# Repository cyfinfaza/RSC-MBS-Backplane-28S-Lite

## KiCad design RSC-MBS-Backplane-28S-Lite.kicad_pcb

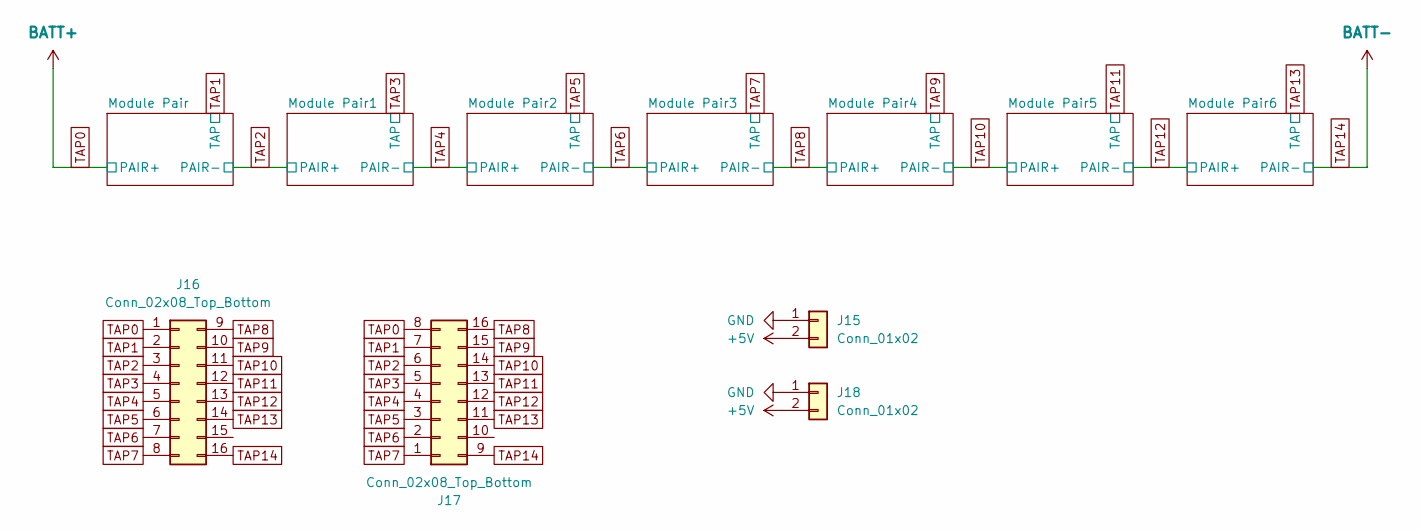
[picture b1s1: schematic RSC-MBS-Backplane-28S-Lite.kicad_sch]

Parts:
J15, J18: Conn_01x02; Molex_Micro-Fit_3.0_43650-0200_1x02_P3.00mm_Horizontal
J16, J17: Conn_02x08_Top_Bottom; Molex_Micro-Fit_3.0_43045-1600_2x08_P3.00mm_Horizontal

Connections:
+5V: J15.2, J18.2; also elsewhere on the board
GND: J15.1, J18.1; also elsewhere on the board
TAP0: J16.1, J17.8; also elsewhere on the board
TAP1: J16.2, J17.7; also elsewhere on the board
TAP2: J16.3, J17.6; also elsewhere on the board
TAP3: J16.4, J17.5; also elsewhere on the board
TAP4: J16.5, J17.4; also elsewhere on the board
TAP5: J16.6, J17.3; also elsewhere on the board
TAP6: J16.7, J17.2; also elsewhere on the board
TAP7: J16.8, J17.1; also elsewhere on the board
TAP8: J16.9, J17.16; also elsewhere on the board
TAP9: J16.10, J17.15; also elsewhere on the board
TAP10: J16.11, J17.14; also elsewhere on the board
TAP11: J16.12, J17.13; also elsewhere on the board
TAP12: J16.13, J17.12; also elsewhere on the board
TAP13: J16.14, J17.11; also elsewhere on the board
TAP14: J16.16, J17.9; also elsewhere on the board

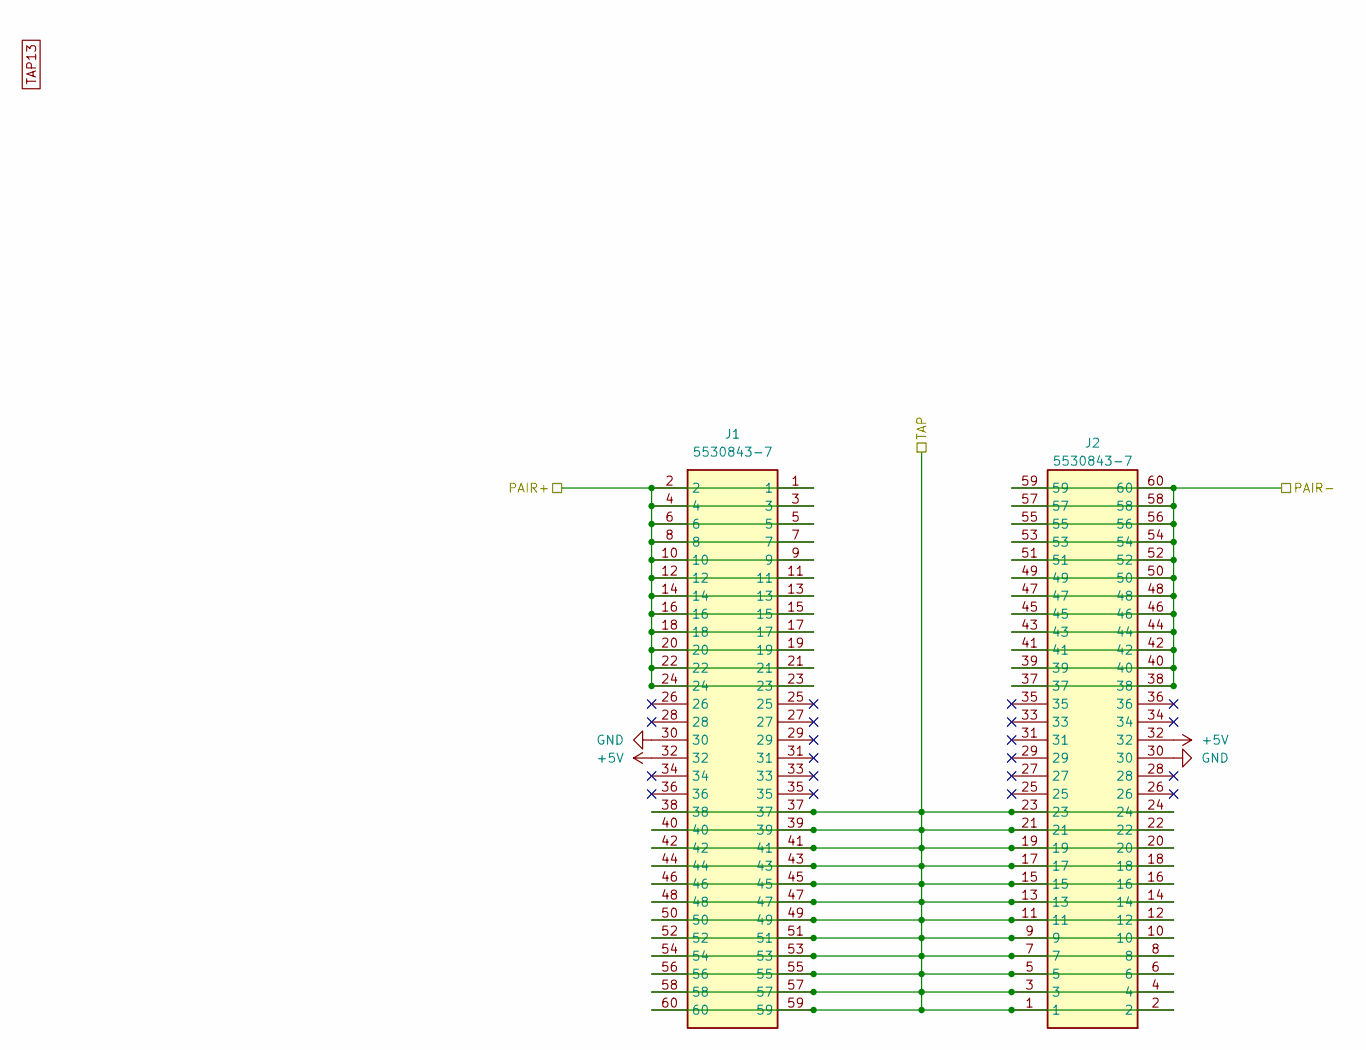
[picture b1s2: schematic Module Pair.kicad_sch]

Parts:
J1, J2: 5530843-7; 55308437; Mouser Part Number 571-5530843-7

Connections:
+5V: J1.32, J2.32; also elsewhere on the board
GND: J1.30, J2.30; also elsewhere on the board
TAP0: J1.1, J1.2, J1.3, J1.4, J1.5, J1.6, J1.7, J1.8, J1.9, J1.10, J1.11, J1.12, J1.13, J1.14, J1.15, J1.16, J1.17, J1.18, J1.19, J1.20, J1.21, J1.22, J1.23, J1.24; also elsewhere on the board
TAP1: J1.37, J1.38, J1.39, J1.40, J1.41, J1.42, J1.43, J1.44, J1.45, J1.46, J1.47, J1.48, J1.49, J1.50, J1.51, J1.52, J1.53, J1.54, J1.55, J1.56, J1.57, J1.58, J1.59, J1.60, J2.1, J2.2, J2.3, J2.4, J2.5, J2.6, J2.7, J2.8, J2.9, J2.10, J2.11, J2.12, J2.13, J2.14, J2.15, J2.16, J2.17, J2.18, J2.19, J2.20, J2.21, J2.22, J2.23, J2.24; also elsewhere on the board
TAP2: J2.37, J2.38, J2.39, J2.40, J2.41, J2.42, J2.43, J2.44, J2.45, J2.46, J2.47, J2.48, J2.49, J2.50, J2.51, J2.52, J2.53, J2.54, J2.55, J2.56, J2.57, J2.58, J2.59, J2.60; also elsewhere on the board

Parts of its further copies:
J3, J4, J5, J6, J7, J8, J9, J10, J11, J12, J13, J14: 5530843-7; 55308437; Mouser Part Number 571-5530843-7

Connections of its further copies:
+5V: J3.32, J4.32, J5.32, J6.32, J7.32, J8.32, J9.32, J10.32, J11.32, J12.32, J13.32, J14.32; also elsewhere on the board
GND: J3.30, J4.30, J5.30, J6.30, J7.30, J8.30, J9.30, J10.30, J11.30, J12.30, J13.30, J14.30; also elsewhere on the board
TAP2: J3.1, J3.2, J3.3, J3.4, J3.5, J3.6, J3.7, J3.8, J3.9, J3.10, J3.11, J3.12, J3.13, J3.14, J3.15, J3.16, J3.17, J3.18, J3.19, J3.20, J3.21, J3.22, J3.23, J3.24; also elsewhere on the board
TAP3: J3.37, J3.38, J3.39, J3.40, J3.41, J3.42, J3.43, J3.44, J3.45, J3.46, J3.47, J3.48, J3.49, J3.50, J3.51, J3.52, J3.53, J3.54, J3.55, J3.56, J3.57, J3.58, J3.59, J3.60, J4.1, J4.2, J4.3, J4.4, J4.5, J4.6, J4.7, J4.8, J4.9, J4.10, J4.11, J4.12, J4.13, J4.14, J4.15, J4.16, J4.17, J4.18, J4.19, J4.20, J4.21, J4.22, J4.23, J4.24; also elsewhere on the board
TAP4: J4.37, J4.38, J4.39, J4.40, J4.41, J4.42, J4.43, J4.44, J4.45, J4.46, J4.47, J4.48, J4.49, J4.50, J4.51, J4.52, J4.53, J4.54, J4.55, J4.56, J4.57, J4.58, J4.59, J4.60, J5.1, J5.2, J5.3, J5.4, J5.5, J5.6, J5.7, J5.8, J5.9, J5.10, J5.11, J5.12, J5.13, J5.14, J5.15, J5.16, J5.17, J5.18, J5.19, J5.20, J5.21, J5.22, J5.23, J5.24; also elsewhere on the board
TAP5: J5.37, J5.38, J5.39, J5.40, J5.41, J5.42, J5.43, J5.44, J5.45, J5.46, J5.47, J5.48, J5.49, J5.50, J5.51, J5.52, J5.53, J5.54, J5.55, J5.56, J5.57, J5.58, J5.59, J5.60, J6.1, J6.2, J6.3, J6.4, J6.5, J6.6, J6.7, J6.8, J6.9, J6.10, J6.11, J6.12, J6.13, J6.14, J6.15, J6.16, J6.17, J6.18, J6.19, J6.20, J6.21, J6.22, J6.23, J6.24; also elsewhere on the board
TAP6: J6.37, J6.38, J6.39, J6.40, J6.41, J6.42, J6.43, J6.44, J6.45, J6.46, J6.47, J6.48, J6.49, J6.50, J6.51, J6.52, J6.53, J6.54, J6.55, J6.56, J6.57, J6.58, J6.59, J6.60, J7.1, J7.2, J7.3, J7.4, J7.5, J7.6, J7.7, J7.8, J7.9, J7.10, J7.11, J7.12, J7.13, J7.14, J7.15, J7.16, J7.17, J7.18, J7.19, J7.20, J7.21, J7.22, J7.23, J7.24; also elsewhere on the board
TAP7: J7.37, J7.38, J7.39, J7.40, J7.41, J7.42, J7.43, J7.44, J7.45, J7.46, J7.47, J7.48, J7.49, J7.50, J7.51, J7.52, J7.53, J7.54, J7.55, J7.56, J7.57, J7.58, J7.59, J7.60, J8.1, J8.2, J8.3, J8.4, J8.5, J8.6, J8.7, J8.8, J8.9, J8.10, J8.11, J8.12, J8.13, J8.14, J8.15, J8.16, J8.17, J8.18, J8.19, J8.20, J8.21, J8.22, J8.23, J8.24; also elsewhere on the board
TAP8: J8.37, J8.38, J8.39, J8.40, J8.41, J8.42, J8.43, J8.44, J8.45, J8.46, J8.47, J8.48, J8.49, J8.50, J8.51, J8.52, J8.53, J8.54, J8.55, J8.56, J8.57, J8.58, J8.59, J8.60, J9.1, J9.2, J9.3, J9.4, J9.5, J9.6, J9.7, J9.8, J9.9, J9.10, J9.11, J9.12, J9.13, J9.14, J9.15, J9.16, J9.17, J9.18, J9.19, J9.20, J9.21, J9.22, J9.23, J9.24; also elsewhere on the board
TAP9: J9.37, J9.38, J9.39, J9.40, J9.41, J9.42, J9.43, J9.44, J9.45, J9.46, J9.47, J9.48, J9.49, J9.50, J9.51, J9.52, J9.53, J9.54, J9.55, J9.56, J9.57, J9.58, J9.59, J9.60, J10.1, J10.2, J10.3, J10.4, J10.5, J10.6, J10.7, J10.8, J10.9, J10.10, J10.11, J10.12, J10.13, J10.14, J10.15, J10.16, J10.17, J10.18, J10.19, J10.20, J10.21, J10.22, J10.23, J10.24; also elsewhere on the board
TAP10: J10.37, J10.38, J10.39, J10.40, J10.41, J10.42, J10.43, J10.44, J10.45, J10.46, J10.47, J10.48, J10.49, J10.50, J10.51, J10.52, J10.53, J10.54, J10.55, J10.56, J10.57, J10.58, J10.59, J10.60, J11.1, J11.2, J11.3, J11.4, J11.5, J11.6, J11.7, J11.8, J11.9, J11.10, J11.11, J11.12, J11.13, J11.14, J11.15, J11.16, J11.17, J11.18, J11.19, J11.20, J11.21, J11.22, J11.23, J11.24; also elsewhere on the board
TAP11: J11.37, J11.38, J11.39, J11.40, J11.41, J11.42, J11.43, J11.44, J11.45, J11.46, J11.47, J11.48, J11.49, J11.50, J11.51, J11.52, J11.53, J11.54, J11.55, J11.56, J11.57, J11.58, J11.59, J11.60, J12.1, J12.2, J12.3, J12.4, J12.5, J12.6, J12.7, J12.8, J12.9, J12.10, J12.11, J12.12, J12.13, J12.14, J12.15, J12.16, J12.17, J12.18, J12.19, J12.20, J12.21, J12.22, J12.23, J12.24; also elsewhere on the board
TAP12: J12.37, J12.38, J12.39, J12.40, J12.41, J12.42, J12.43, J12.44, J12.45, J12.46, J12.47, J12.48, J12.49, J12.50, J12.51, J12.52, J12.53, J12.54, J12.55, J12.56, J12.57, J12.58, J12.59, J12.60, J13.1, J13.2, J13.3, J13.4, J13.5, J13.6, J13.7, J13.8, J13.9, J13.10, J13.11, J13.12, J13.13, J13.14, J13.15, J13.16, J13.17, J13.18, J13.19, J13.20, J13.21, J13.22, J13.23, J13.24; also elsewhere on the board
TAP13: J13.37, J13.38, J13.39, J13.40, J13.41, J13.42, J13.43, J13.44, J13.45, J13.46, J13.47, J13.48, J13.49, J13.50, J13.51, J13.52, J13.53, J13.54, J13.55, J13.56, J13.57, J13.58, J13.59, J13.60, J14.1, J14.2, J14.3, J14.4, J14.5, J14.6, J14.7, J14.8, J14.9, J14.10, J14.11, J14.12, J14.13, J14.14, J14.15, J14.16, J14.17, J14.18, J14.19, J14.20, J14.21, J14.22, J14.23, J14.24; also elsewhere on the board
TAP14: J14.37, J14.38, J14.39, J14.40, J14.41, J14.42, J14.43, J14.44, J14.45, J14.46, J14.47, J14.48, J14.49, J14.50, J14.51, J14.52, J14.53, J14.54, J14.55, J14.56, J14.57, J14.58, J14.59, J14.60; also elsewhere on the board

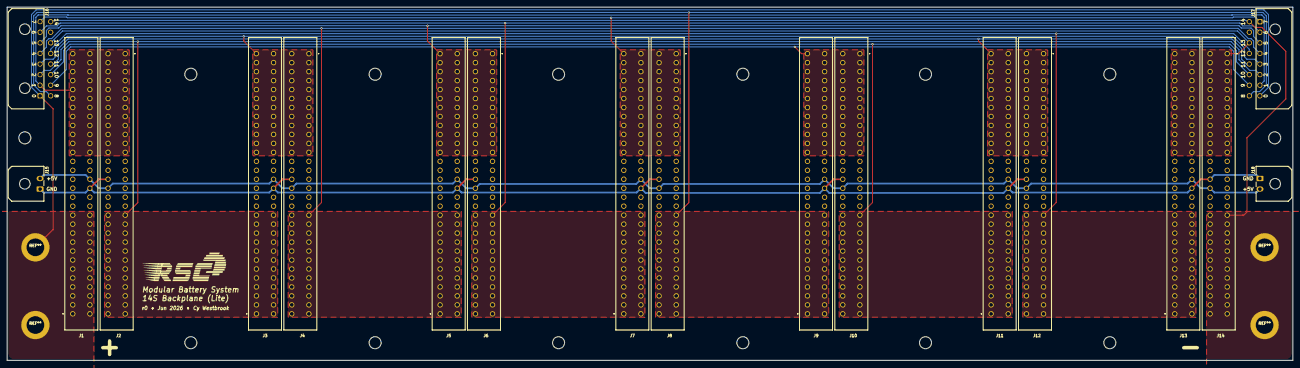
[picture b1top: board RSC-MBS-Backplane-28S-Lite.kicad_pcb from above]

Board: 2 copper layers, 364.0 x 100.0 mm, 18 parts (0 on the bottom side), 17 nets.

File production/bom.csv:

Designator,Footprint,Quantity,Value,LCSC Part #
"J1, J10, J11, J12, J13, J14, J2, J3, J4, J5, J6, J7, J8, J9",55308437,14,5530843-7,
"J15, J18",Molex_Micro-Fit_3.0_43650-0200_1x02_P3.00mm_Horizontal,2,Conn_01x02,
"J16, J17",Molex_Micro-Fit_3.0_43045-1600_2x08_P3.00mm_Horizontal,2,Conn_02x08_Top_Bottom,

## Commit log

2026-06-17 initial attempt at routing balance traces
2026-06-18 complete initial routing, layout, and silkscreen
2026-06-22 r0 final
